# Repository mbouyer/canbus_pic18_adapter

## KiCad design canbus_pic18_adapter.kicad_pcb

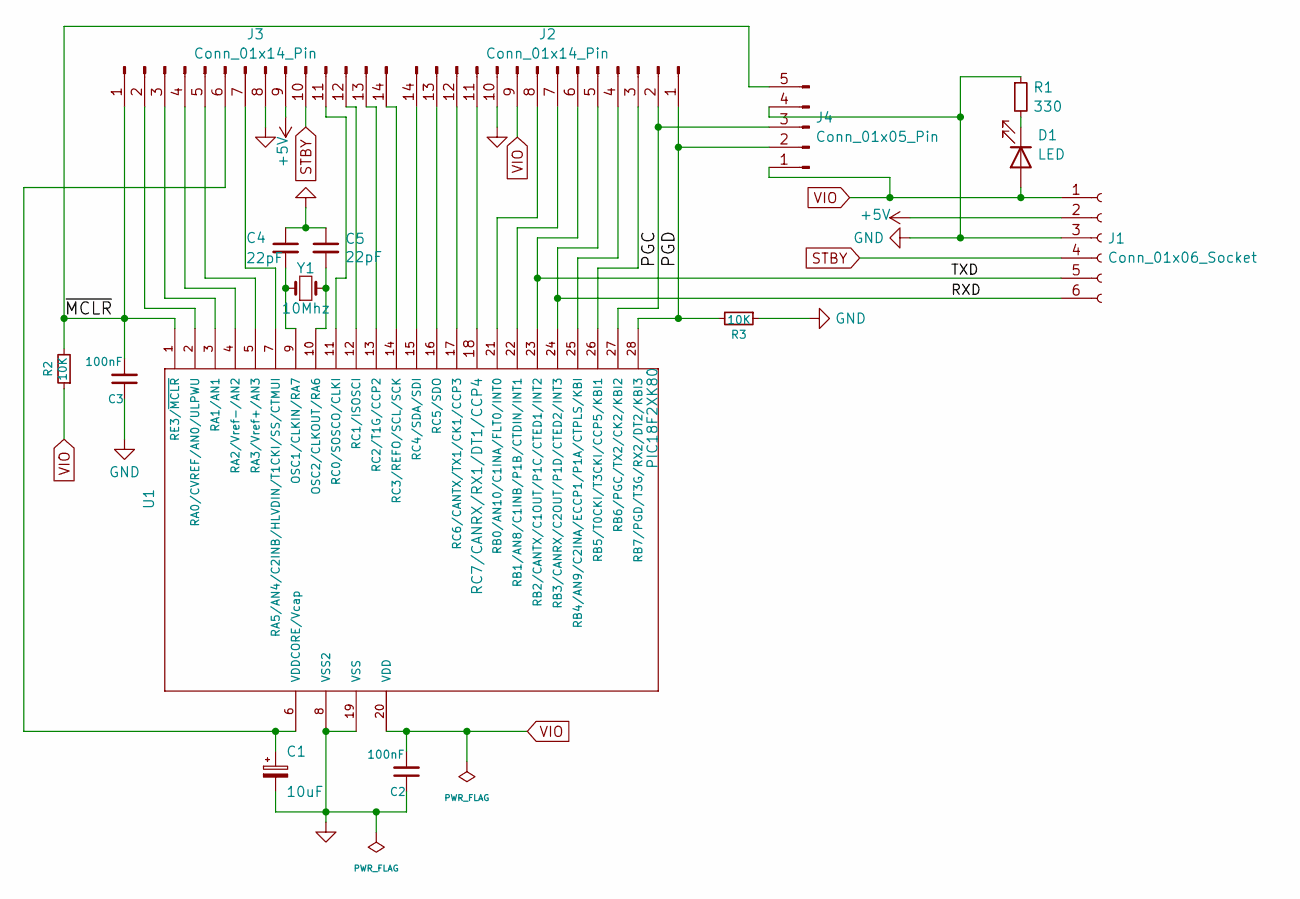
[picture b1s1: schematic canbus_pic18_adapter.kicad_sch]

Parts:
C1: 10uF; C_0805_2012Metric_Pad1.18x1.45mm_HandSolder
C2, C3: 100nF; C_0603_1608Metric_Pad1.08x0.95mm_HandSolder
C4, C5: 22pF; C_Disc_D3.4mm_W2.1mm_P2.50mm
D1: LED; LED_D3.0mm
J1: Conn_01x06_Socket; PinSocket_1x06_P2.54mm_Horizontal
J2, J3: Conn_01x14_Pin; PinHeader_1x14_P2.54mm_Vertical
J4: Conn_01x05_Pin; PinHeader_1x05_P2.54mm_Vertical
R1: 330; R_Axial_DIN0309_L9.0mm_D3.2mm_P12.70mm_Horizontal
R2, R3: 10K; R_0805_2012Metric_Pad1.20x1.40mm_HandSolder
U1: PIC18F2XK80; DIP-28_W7.62mm_Socket
Y1: 10Mhz; Crystal_HC18-U_Vertical

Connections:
+5V: J1.2, J3.9
/PGC: J2.2, J4.3, U1.27 (RB6/PGC/TX2/CK2/KBI2)
/PGD: J2.1, J4.2, R3.2, U1.28 (RB7/PGD/T3G/RX2/DT2/KBI3)
/RXD: J1.6, J2.5, U1.24 (RB3/CANRX/C2OUT/P1D/CTED2/INT3)
/TXD: J1.5, J2.6, U1.23 (RB2/CANTX/C1OUT/P1C/CTED1/INT2)
/~MCLR: C3.2, J3.1, J4.5, R2.2, U1.1 (RE3/~MCLR)
unnamed: D1.1 (K), R1.2
unnamed: J2.3, U1.26 (RB5/T0CKI/T3CKI/CCP5/KBI1)
unnamed: J2.4, U1.25 (RB4/AN9/C2INA/ECCP1/P1A/CTPLS/KBI)
unnamed: J2.7, U1.22 (RB1/AN8/C1INB/P1B/CTDIN/INT1)
unnamed: J2.8, U1.21 (RB0/AN10/C1INA/FLT0/INT0)
unnamed: J2.11, U1.18 (RC7/CANRX/RX1/DT1/CCP4)
unnamed: J2.12, U1.17 (RC6/CANTX/TX1/CK1/CCP3)
unnamed: J2.13, U1.16 (RC5/SDO)
unnamed: J2.14, U1.15 (RC4/SDA/SDI)
unnamed: J3.2, U1.2 (RA0/CVREF/AN0/ULPWU)
unnamed: J3.3, U1.3 (RA1/AN1)
unnamed: J3.4, U1.4 (RA2/Vref-/AN2)
unnamed: J3.5, U1.5 (RA3/Vref+/AN3)
unnamed: C1.1, J3.6, U1.6 (VDDCORE/Vcap)
unnamed: J3.7, U1.7 (RA5/AN4/C2INB/HLVDIN/T1CKI/SS/CTMUI)
unnamed: J3.11, U1.11 (RC0/SOSCO/CLKI)
unnamed: J3.12, U1.12 (RC1/ISOSCI)
unnamed: J3.13, U1.13 (RC2/T1G/CCP2)
unnamed: J3.14, U1.14 (RC3/REFO/SCL/SCK)
unnamed: C4.2, U1.9 (OSC1/CLKIN/RA7), Y1.1
unnamed: C5.2, U1.10 (OSC2/CLKOUT/RA6), Y1.2
STBY: J1.4, J3.10

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
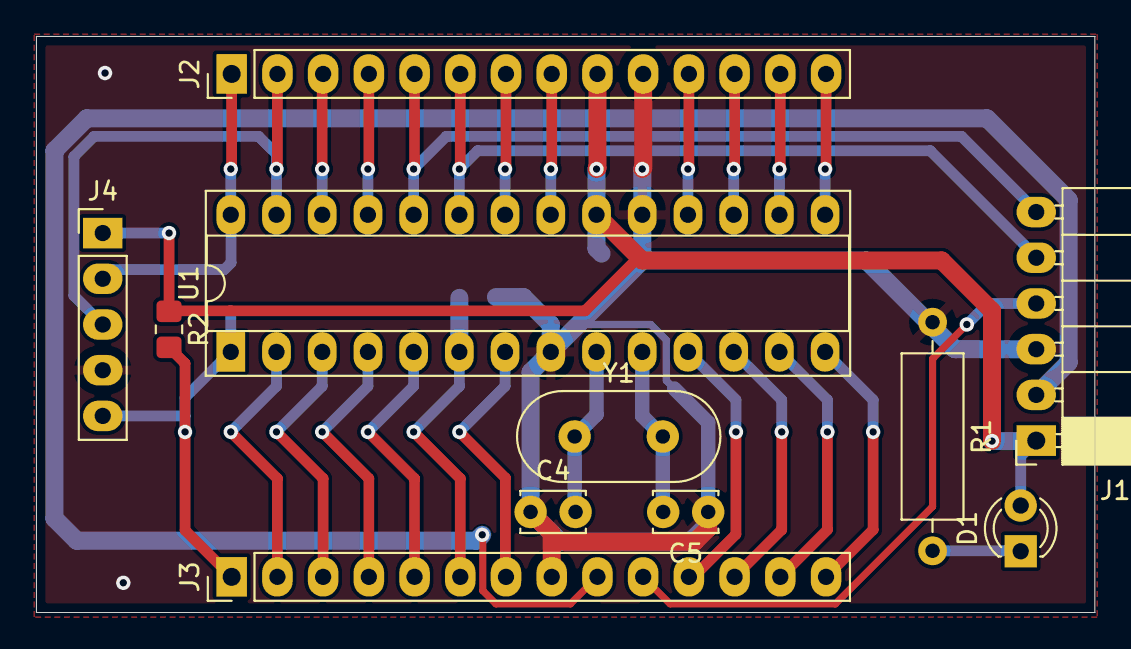
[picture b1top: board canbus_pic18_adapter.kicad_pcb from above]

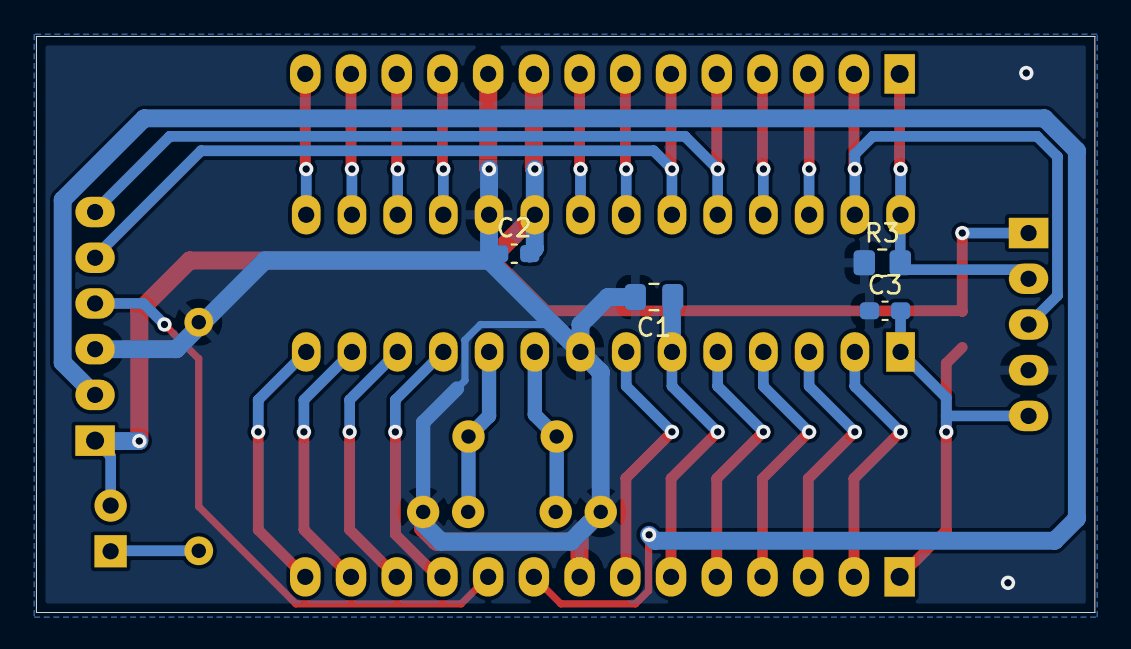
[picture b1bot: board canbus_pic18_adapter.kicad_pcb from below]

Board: 2 copper layers, 58.8 x 32.0 mm, 15 parts (4 on the bottom side), 30 nets.

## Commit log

2024-09-23 Initial schematic commit
2024-09-24 Add programming header Add a LED on VIO Other minor adjustemnts
2024-09-24 Route board
2024-09-24 Add local libraries
2024-09-24 pass DRC
